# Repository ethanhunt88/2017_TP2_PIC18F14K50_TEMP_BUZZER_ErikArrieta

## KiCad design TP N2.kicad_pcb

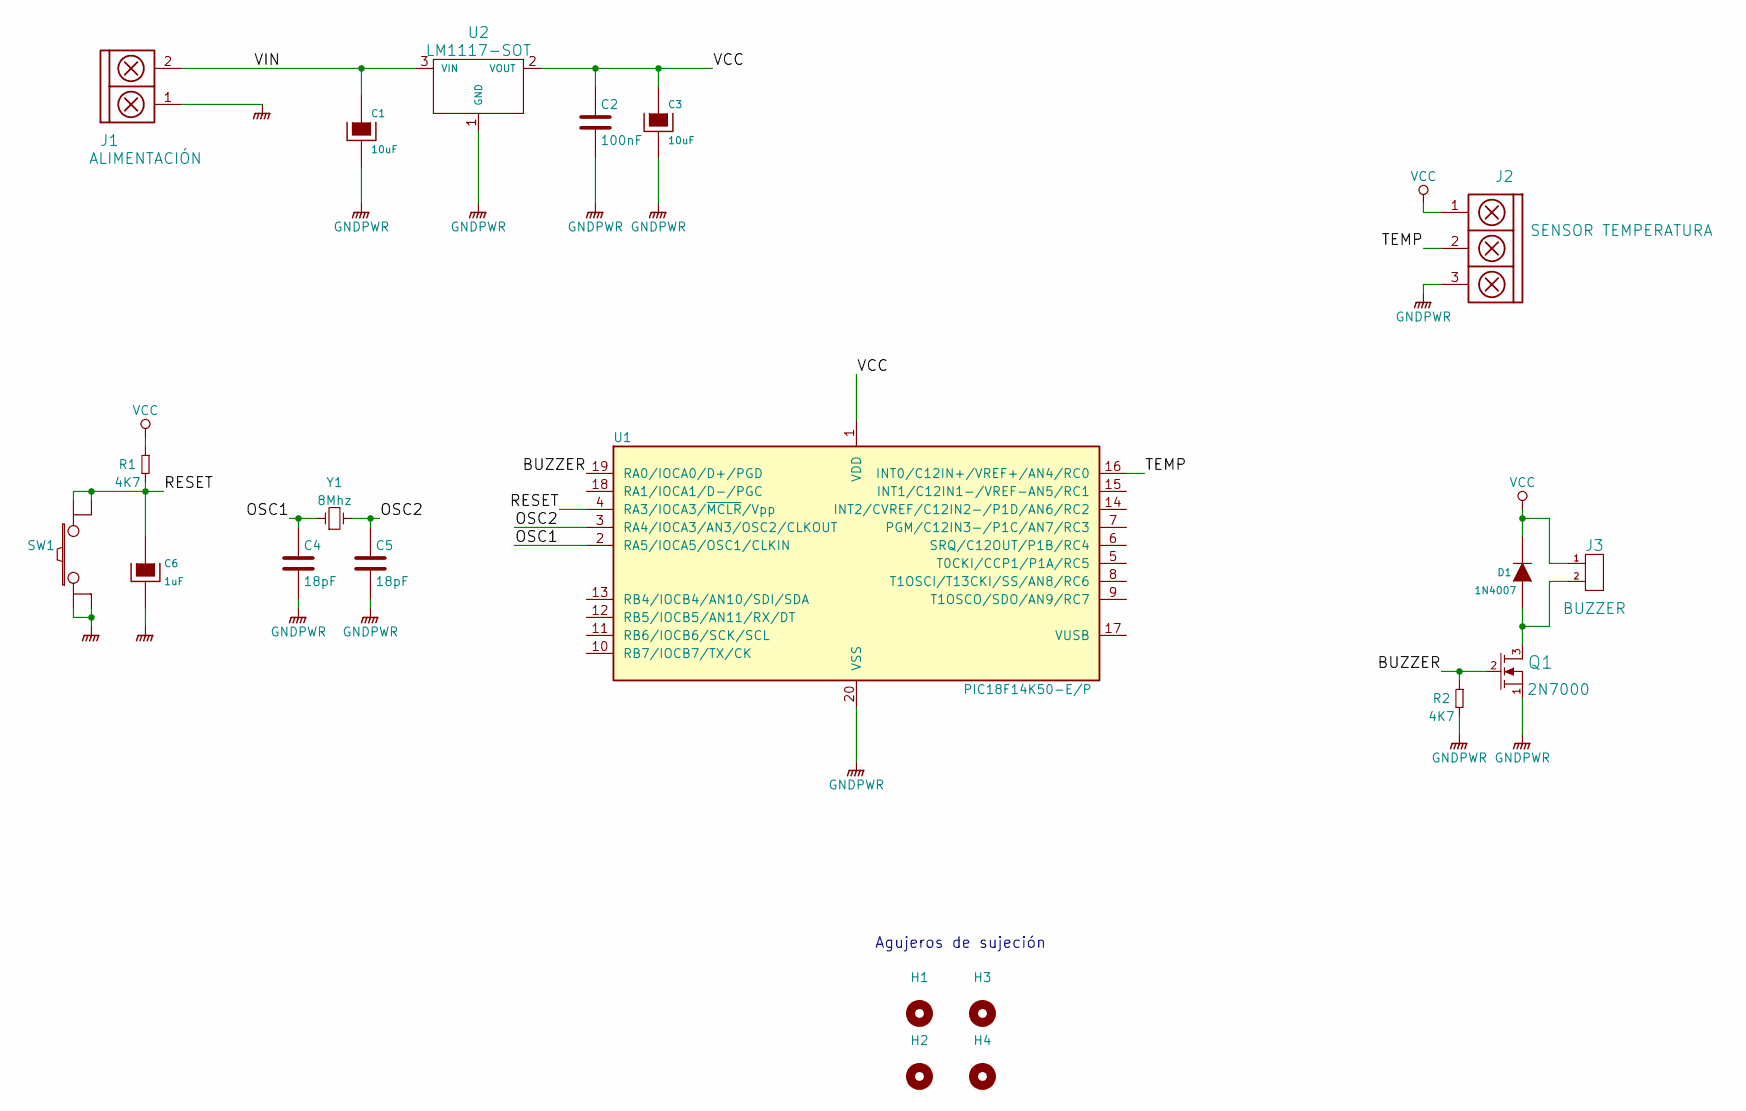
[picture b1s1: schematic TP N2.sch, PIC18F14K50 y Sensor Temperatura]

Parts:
C1, C3: 10uF; CAP_ELEC_5x11mm
C2: 100nF; C_1206
C4, C5: 18pF; C_1206
C6: 1uF; CAP_ELEC_5x11mm
D1: 1N4007; DO-41
H1, H2, H3, H4: Mounting_Hole; Tornillo_M3_8mm
J1: ALIMENTACIÓN; BORNERA2_AZUL
J2: SENSOR TEMPERATURA; BORNERA3_AZUL
J3: BUZZER; Pin_strip_2
Q1: 2N7000; to92
R1, R2: 4K7; R_1206
SW1: RST; Pulsador_TH_4
U1: PIC18F14K50-E/P; DIP_20-300_socket
U2: LM1117-SOT; SOT223
Y1: 8Mhz; HC49S

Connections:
/BUZZER: Q1.2 (G), R2.1, U1.19 (RA0/IOCA0/D+/PGD)
/OSC1: C4.1, U1.2 (RA5/IOCA5/OSC1/CLKIN), Y1.1
/OSC2: C5.1, U1.3 (RA4/IOCA3/AN3/OSC2/CLKOUT), Y1.2
/RESET: C6.1, R1.2, SW1.3, SW1.4, U1.4 (RA3/IOCA3/~MCLR~/Vpp)
/TEMP: J2.2, U1.16 (INT0/C12IN+/VREF+/AN4/RC0)
/VIN: C1.1, J1.2, U2.3 (VIN)
GNDPWR: C1.2, C2.2, C3.2, C4.2, C5.2, C6.2, J1.1, J2.3, Q1.1 (S), R2.2, SW1.1, SW1.2, U1.20 (VSS), U2.1 (GND)
unnamed: D1.1 (A), J3.2, Q1.3 (D)
VCC: C2.1, C3.1, D1.2 (K), J2.1, J3.1, R1.1, U1.1 (VDD), U2.2 (VOUT)

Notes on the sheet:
Agujeros de sujeción

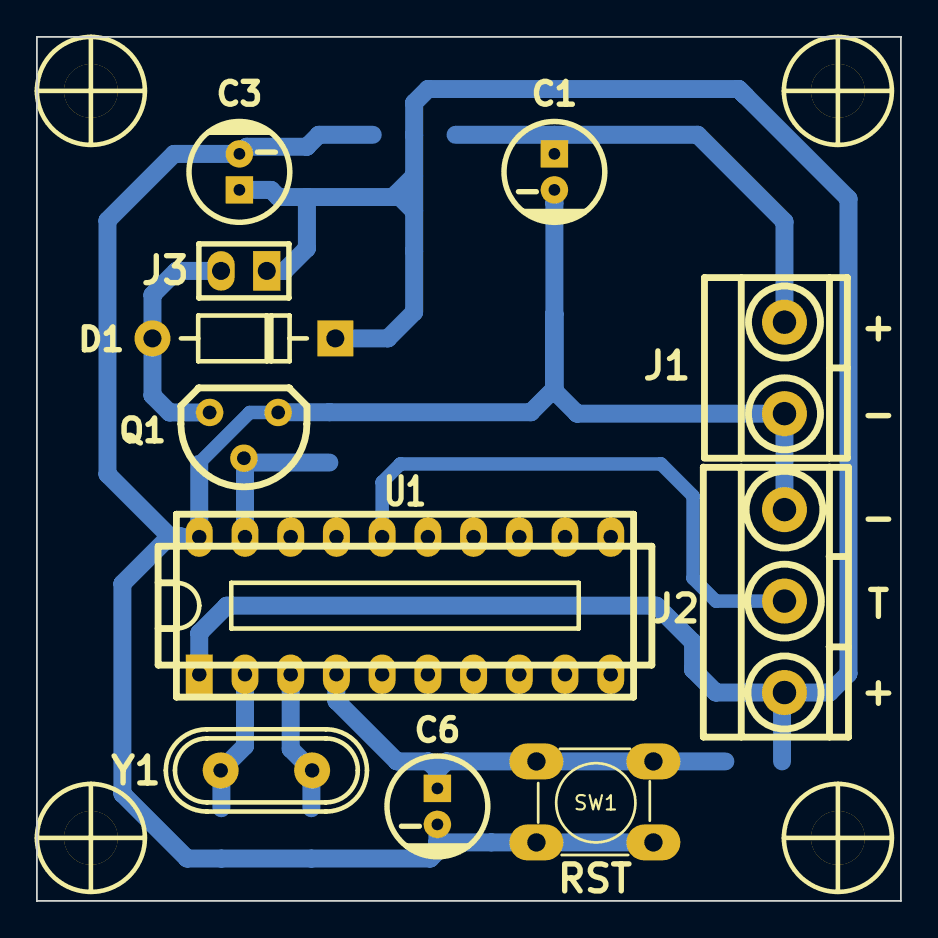
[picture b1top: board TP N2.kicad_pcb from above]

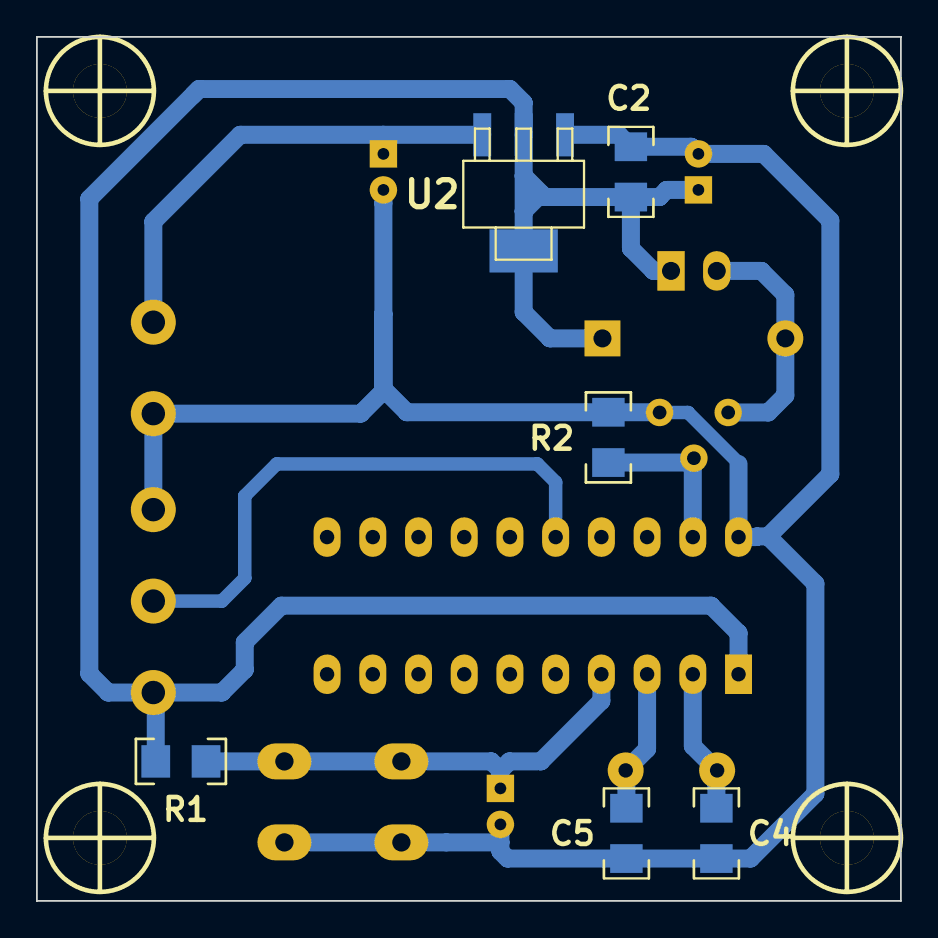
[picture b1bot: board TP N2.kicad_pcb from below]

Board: 2 copper layers, 48.0 x 48.0 mm, 21 parts (6 on the bottom side), 9 nets.

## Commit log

2018-03-25 Versión inicial
